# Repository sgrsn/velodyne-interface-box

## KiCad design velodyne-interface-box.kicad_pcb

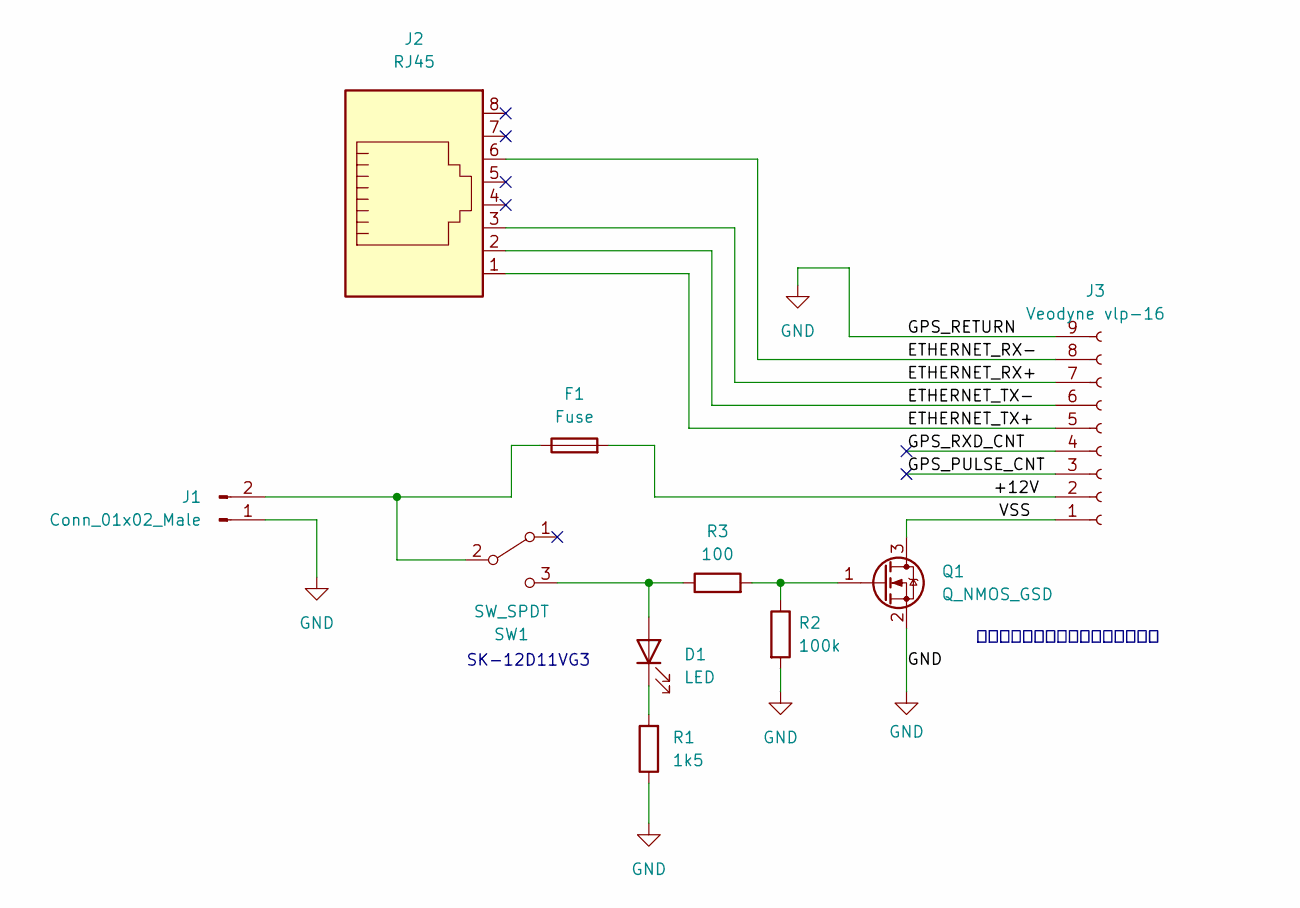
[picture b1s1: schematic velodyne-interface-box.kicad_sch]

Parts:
D1: LED; LED_0603_1608Metric
F1: Fuse; Fuseholder_Blade_Mini_Keystone_3568
J1: Conn_01x02_Male; AMASS_XT30PW-M_1x02_P2.50mm_Horizontal
J2: RJ45; RJ45_Wuerth_7499010001A_Horizontal
J3: Veodyne vlp-16; TerminalBlock_TE_282834-9_1x09_P2.54mm_Horizontal
Q1: Q_NMOS_GSD; SOT-23W
R1: 1k5; R_0603_1608Metric
R2: 100k; R_0603_1608Metric
R3: 100; R_0603_1608Metric
SW1: SW_SPDT; SW_CuK_OS102011MA1QN1_SPDT_Angled

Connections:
/+12V: F1.2, J3.2
/ETHERNET_RX+: J2.3, J3.7
/ETHERNET_RX-: J2.6, J3.8
/ETHERNET_TX+: J2.1, J3.5
/ETHERNET_TX-: J2.2, J3.6
/GPS_PULSE_CNT: J3.3
/GPS_RXD_CNT: J3.4
/VSS: J3.1, Q1.3 (D)
GND: J1.1, J3.9, Q1.2 (S), R1.1, R2.2
unnamed: D1.1 (K), R1.2
unnamed: D1.2 (A), R3.1, SW1.3 (C)
unnamed: F1.1, J1.2, SW1.2 (B)
unnamed: Q1.1 (G), R2.1, R3.2

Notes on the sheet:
ＩＲＦＭＬ８２４４ＴＲＰＢＦＴＲ
SK-12D11VG3

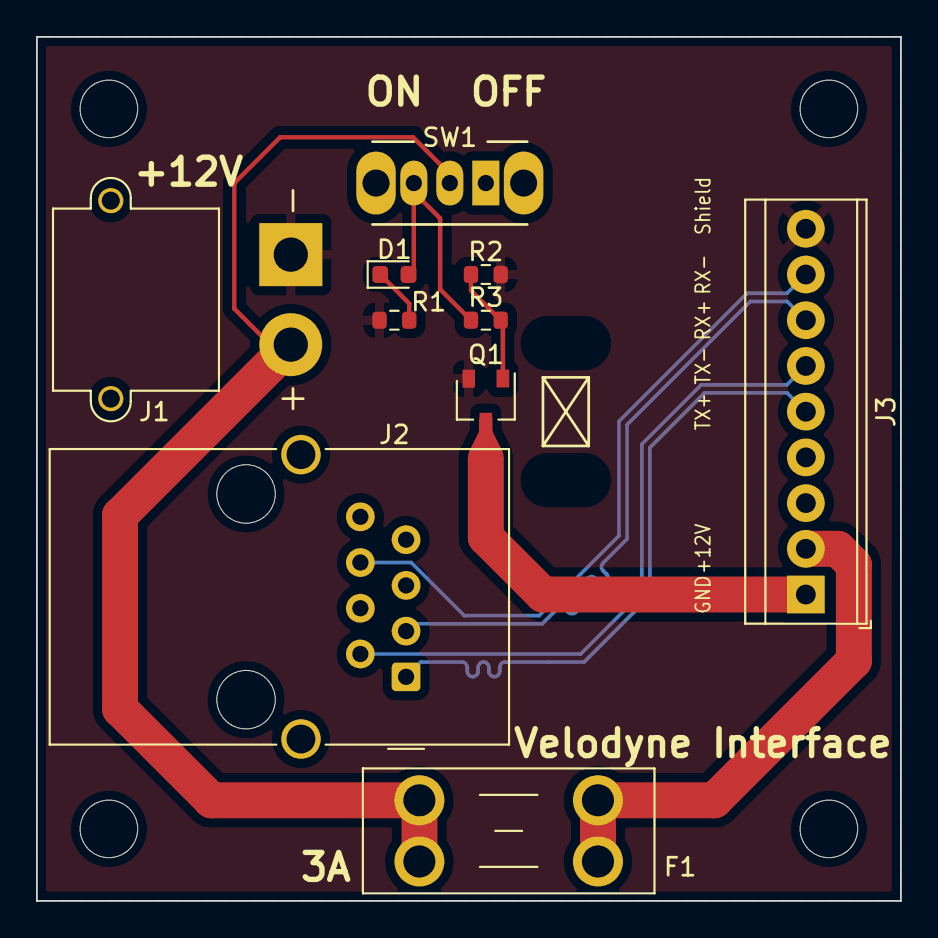
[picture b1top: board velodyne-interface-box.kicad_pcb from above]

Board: 2 copper layers, 48.0 x 48.0 mm, 10 parts (0 on the bottom side), 11 nets.
